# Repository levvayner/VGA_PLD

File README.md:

# VGA Video Card
This project uses TTL components and 2 GALs to create a video card.
There are several parts to the entire development system to aid in development and troubleshooting. Another repository for code that is used on the Arduino Due can be found at https://github.com/levvayner/SRAM-Console

## Parts
 - Hardware Design files in KiCad
 - 2 projects for progamming GAL22V10C PLDs
 - Application used to refine and upload images to the Arduino Due
 - Timing and other documentation
 - Firmware for the Arduino Due to host the video card (https://github.com/levvayner/SRAM-Console)

 ## Getting Started

 ### Prerequisites
 #### Schematics
KiCad software - available for free @ https://www.kicad.org/
 #### Programmable Logic Devices
This can be done with the official Atmel software (https://www.microchip.com/en-us/products/fpgas-and-plds/spld-cplds/pld-design-resources) on windows and using their programmer. 
An alternative approach is to use a cheap progammer like the **TL866+** and using Microsoft Code with the **VS Cupl** extension.
 -http://www.xgecu.com/en/TL866_main.html
-https://marketplace.visualstudio.com/items?itemName=VaynerSystems.VS-Cupl

If choosing the former, follow Atmel's instructions using the included .pld files. If chosing the latter, you can open the workspace and you will see both projects. You can build and deploy the projects right from Code!

You will need to download the Atmel Wincupl progam either way. If you chose to use VS code, you will also need to download and install minipro. More instructions about requirements can be found in the VS Cupl repo https://github.com/levvayner/ATF15xx-cupl

#### Microcontroller
The project uses an Arduino Due uC. The device is low cost, offers a great deal of pins, and has a low price point.

Another device like the Arduino MEGA may suffice. 
Install Microsoft's Code and install the Platform IO extension.
The project can be found here: https://github.com/levvayner/SRAM-Console

## Building the hardware

You can use a breadboard and follow the schematic to build the circuit. First the clock and counters are wired. Then the PLDs are wired to execute combinatory logic to determine timing signals like V-SYNC, H-SYNC, and others like when the screen is not displaying, marking it safe to write to RAM.

The components used in the schematic are available in the KiCad project's output folder.
Currently they are

| Component                 | Source                                                                                 |
| ------------------------- | -------------------------------------------------------------------------------------- |
| Arduino Due               | https://docs.arduino.cc/hardware/due                                                   |
| Capactitor (0805) 560 pf  | ebay, mouser, digikey                                                                  |
| Capacitor Tantalum        | ebay, mouser, digikey                                                                  |
| 2.54mm pins               | ebay, mouser, digikey                                                                  |
| DSUB 15 pin VGA connector | ebay, mouser, digikey                                                                  |
| USB type A connector      | ebay, mouser, digikey                                                                  |
| Resistors (0805)          | ebay, mouser, digikey                                                                  |
| K6X8008T2B-TF55           | https://www.alldatasheet.com/datasheet-pdf/download/85484/SAMSUNG/K6X8008C2B-TF55.html |
| 74HC245D                  | ebay, mouser, digikey                                                                  |
| 74HC161D                  | ebay, mouser, digikey                                                                  |
| 74HC32D                   | ebay, mouser, digikey                                                                  |
| 74HC08D                   | ebay, mouser, digikey                                                                  |
| 74HC00D                   | ebay, mouser, digikey                                                                  |
| 74HC14D                   | ebay, mouser, digikey                                                                  |
| GAL22V10                  | ebay, mouser, digikey                                                                  |
| 16MHz Full can oscillator | ebay, mouser, digikey                                                                  |

### GALs
The programmable logic devices are not absolutely required. They can be replaced by inverters and a few logic gates to determine when a counter should trigger a signal (e.g. h-sync at count 603) and use the counter inputs to determine if that number is reached. Several flip flops can be used for storing the state e.g. store v-sync bit at frame 610, clear at 620.
However you may want to change timings or the clock speed to accomplish a different resolution or pixel density. It is much easier to reprogram the GALS to change timing than to re-wire these logic gates. If you have finalized your design, chaning to logic gates and flip flops is recommended. Even better you can use a magnitude comperator instead of a collection of logic gates.

>To progam the gals, you may need to erase the chip. Some chips come locked, and the programmer software from XGECU has an option to clear it. If your changes don't seem to take affect after programming, use their software to make sure the chip is not locked.

There are two projects included. One is used for the horizontal timing, the other for vertical.

>*There is **VGA_SINGLE_PLD** project that can use an **ATF1504AS** instead of these two, but it has not been verified.*

### Arduino 
The project [VGA Controller](https://github.com/levvayner/SRAM-Console) can be used to interface with and develop the video card further. It has functionality to connect to the controller from its serial port, or connect a PS/2 keyboard (experimental) 

## Roadmap
- Add PS/2 mouse support
- Add second SRAM chip to expand data bus to 16 bit
- Add second SRAM chip to round-robin 2 chips between controller and video output, allowing for controller to read/write to SRAM without interfering with the VGA rendering process.

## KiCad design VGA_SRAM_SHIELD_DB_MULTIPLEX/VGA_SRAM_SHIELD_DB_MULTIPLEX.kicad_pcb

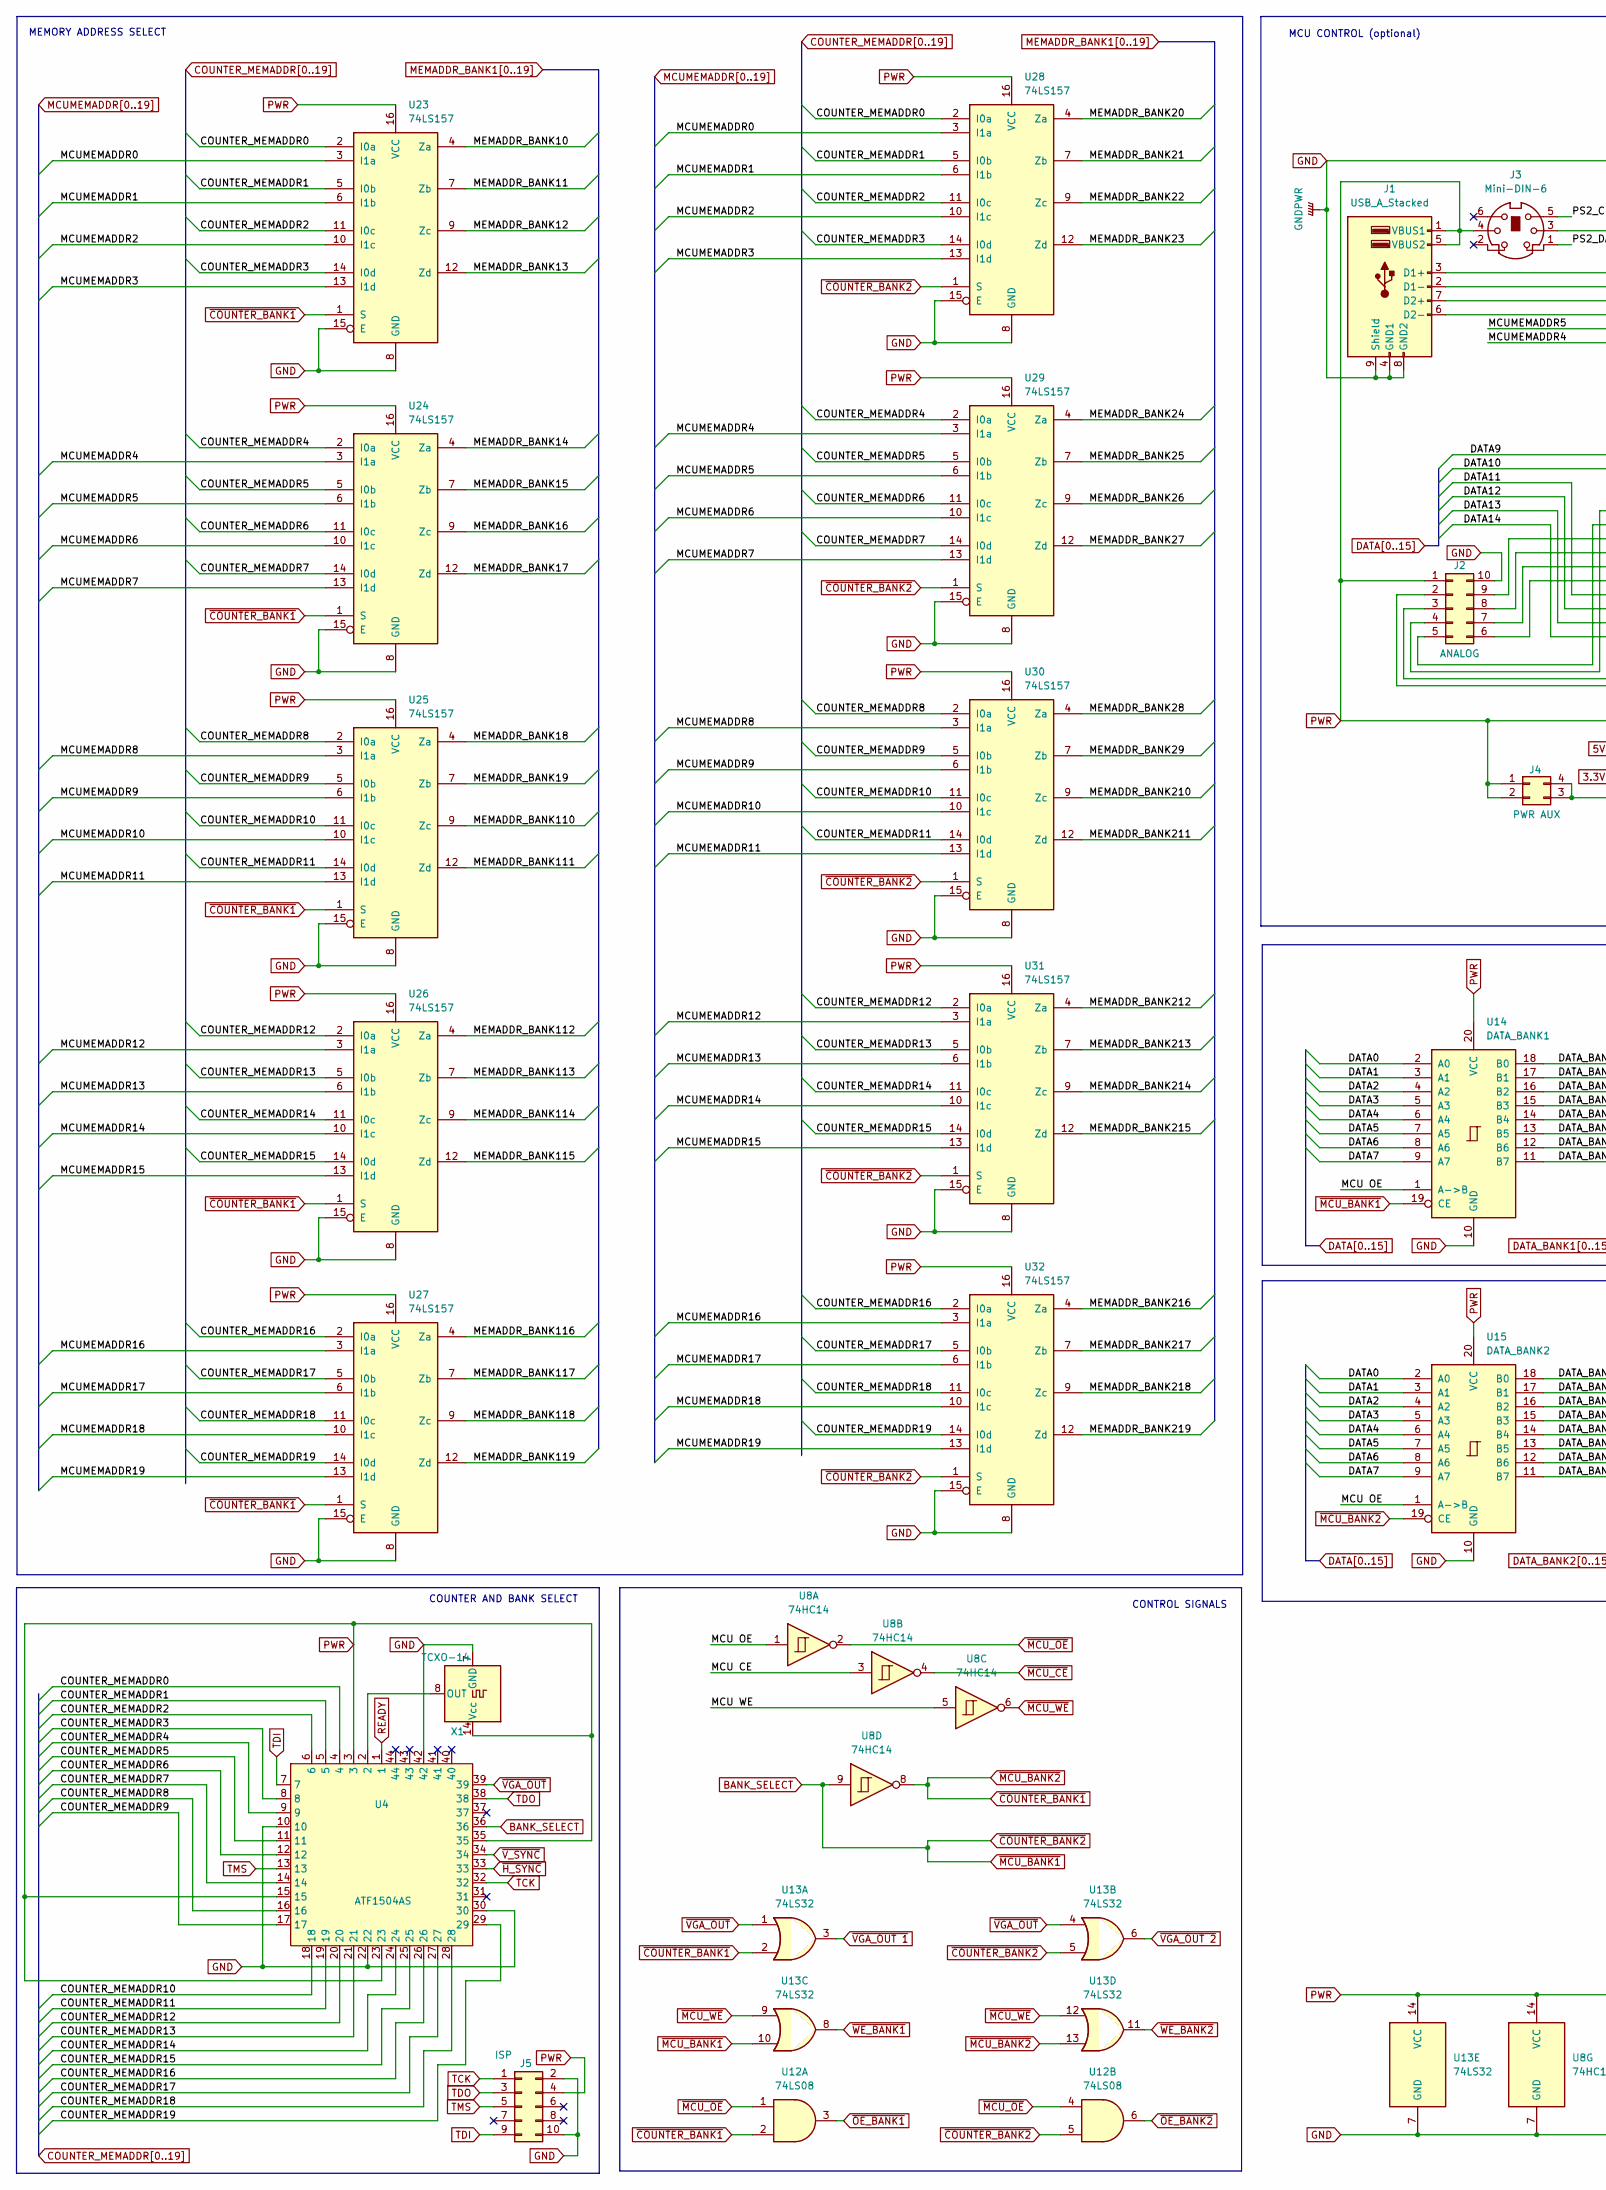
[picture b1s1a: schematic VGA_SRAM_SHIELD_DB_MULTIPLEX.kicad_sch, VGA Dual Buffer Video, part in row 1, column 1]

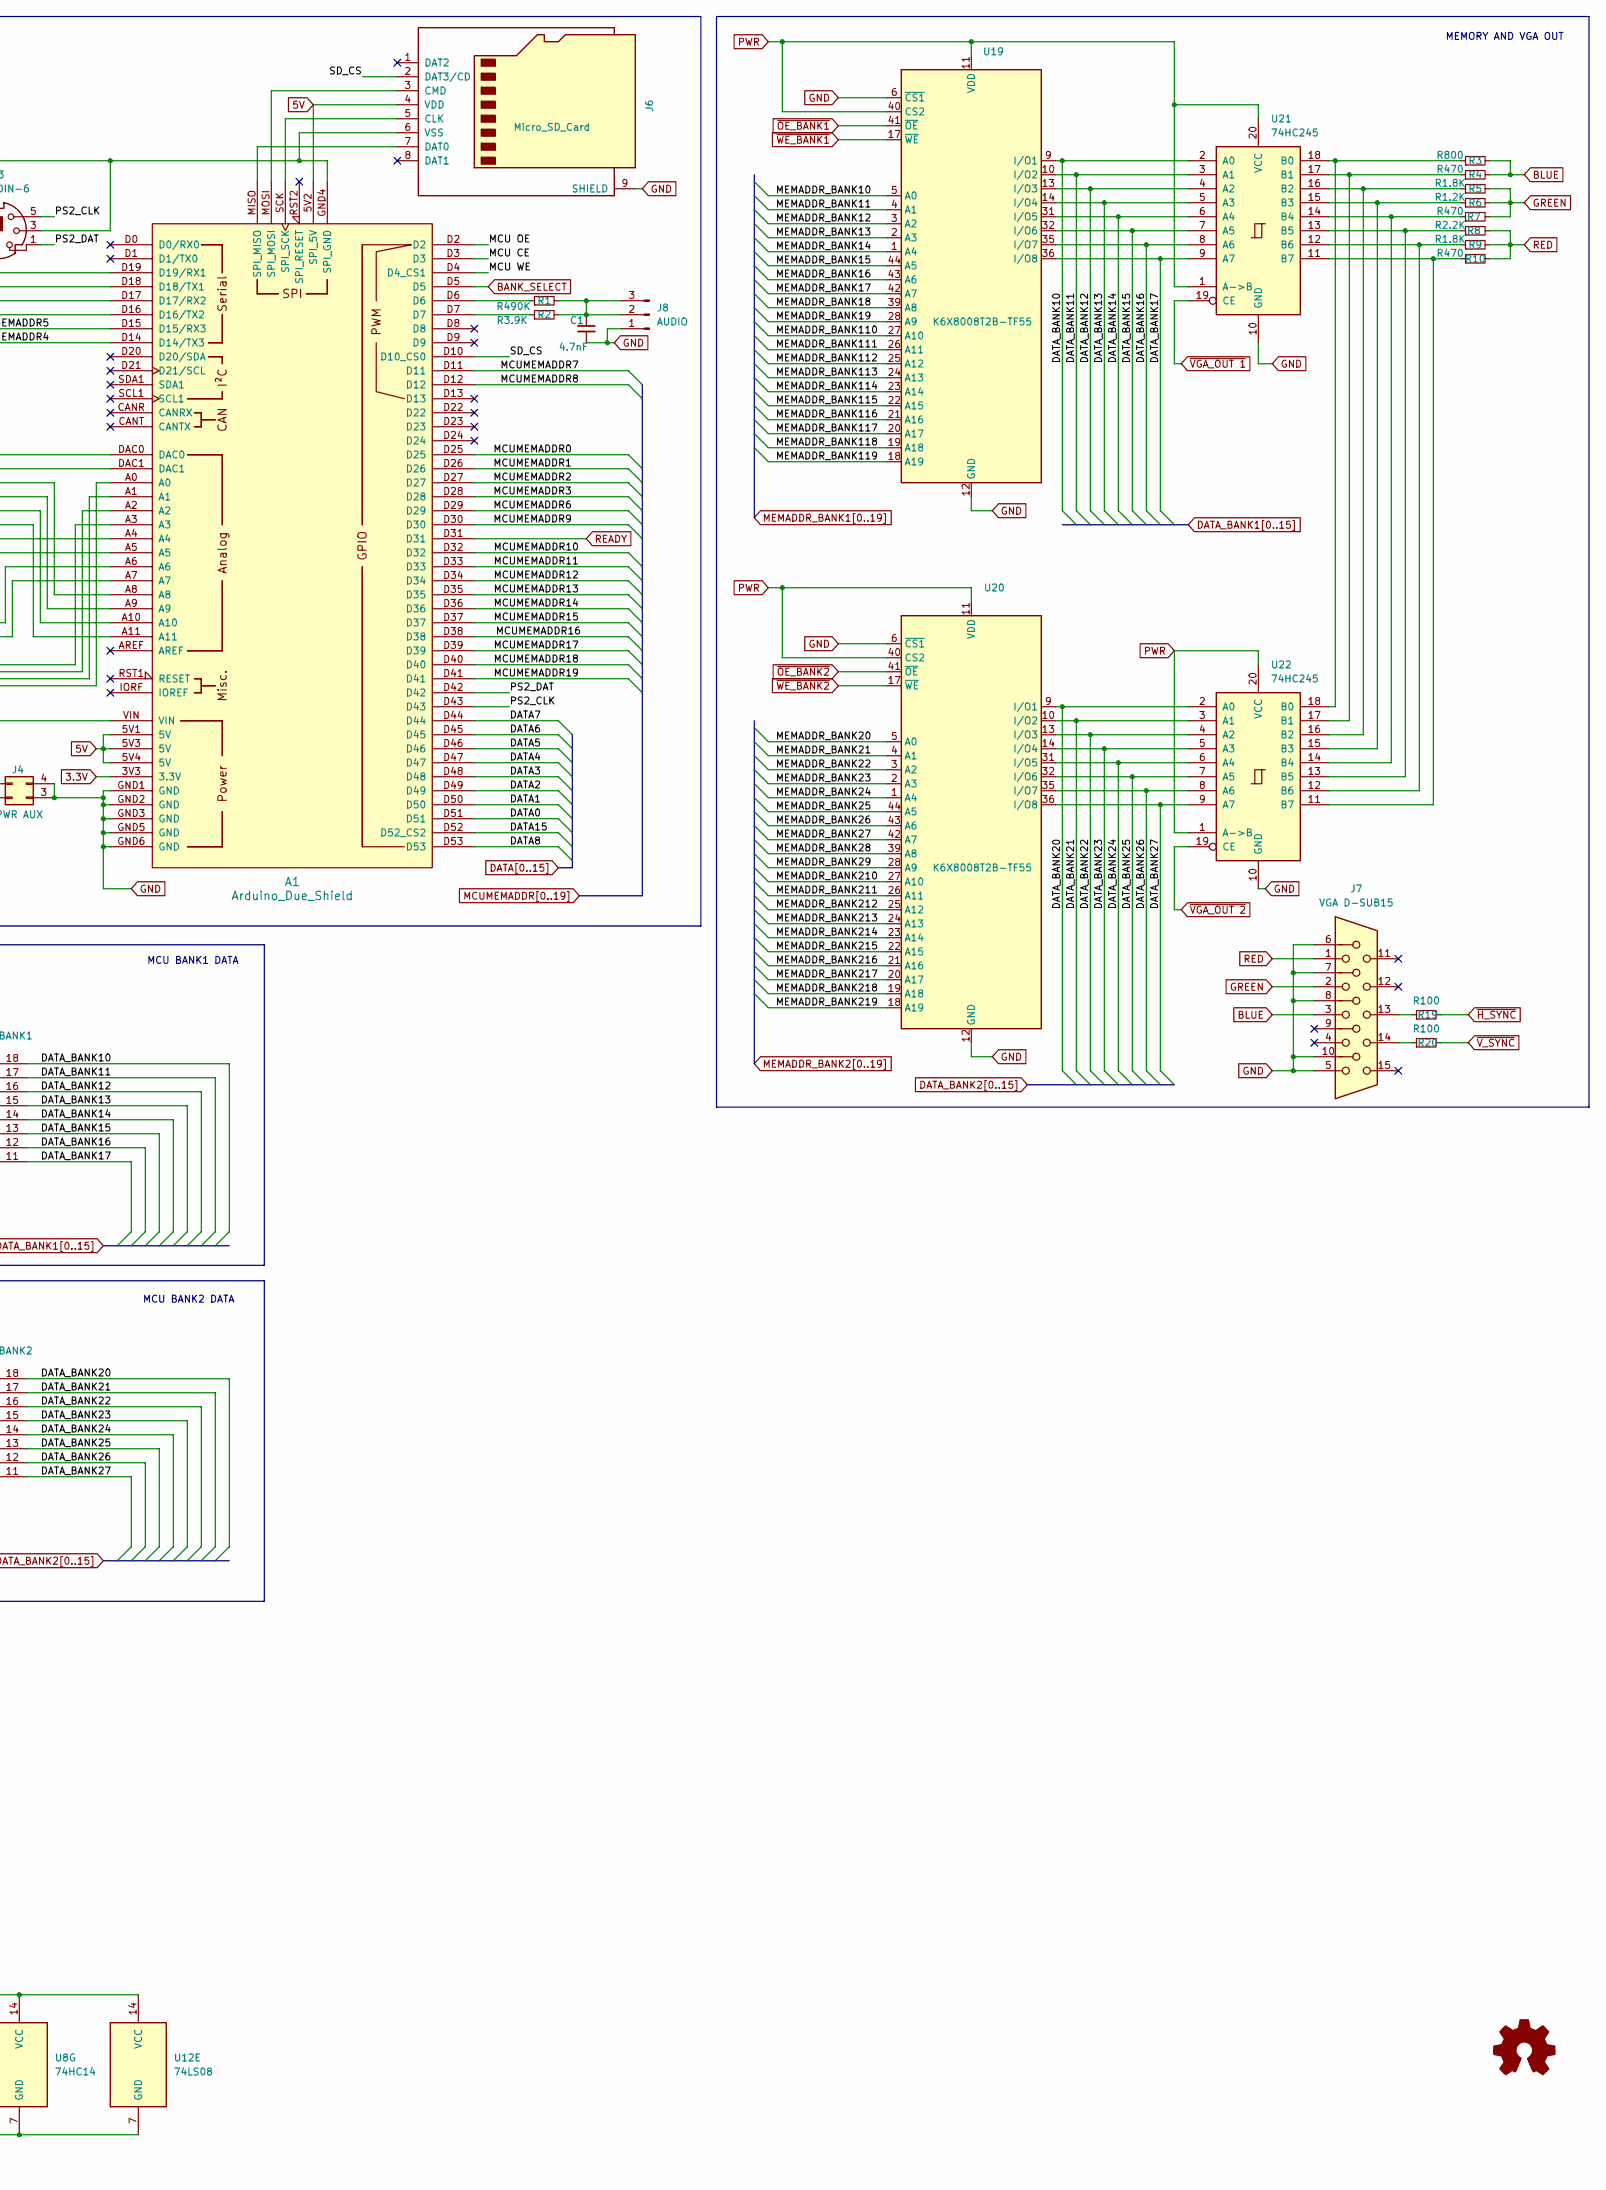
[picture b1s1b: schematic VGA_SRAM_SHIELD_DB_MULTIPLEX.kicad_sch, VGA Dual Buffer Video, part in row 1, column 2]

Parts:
A1: Arduino_Due_Shield
C1: 4.7nF; C_0805_2012Metric
J1: USB_A_Stacked; USB_A_CUI_UJ2-ADH-TH_Horizontal_Stacked
J2: ANALOG; PinSocket_2x05_P2.54mm_Vertical
J3: Mini-DIN-6; mini-DIN 6
J4: PWR AUX; PinSocket_2x02_P2.54mm_Vertical
J5: ISP; PinSocket_2x05_P2.54mm_Vertical
J6: Micro_SD_Card; J_SD_Card-micro_socket_A
J7: VGA D-SUB15; DSUB-15-HD_Female_Horizontal_P2.29x1.98mm_EdgePinOffset8.35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
J8: AUDIO; PinSocket_1x03_P2.54mm_Vertical
R1: R490K; R_0805_2012Metric
R2: R3.9K; R_0805_2012Metric
R3: R800; R_0805_2012Metric
R4, R7, R10: R470; R_0805_2012Metric
R5, R9: R1.8K; R_0805_2012Metric
R6: R1.2K; R_0805_2012Metric
R8: R2.2K; R_0805_2012Metric
R19, R20: R100; R_0805_2012Metric
U4: ATF1504AS; PLCC-44_THT-Socket
U8: 74HC14; SO-14_3.9x8.65mm_P1.27mm
U12: 74LS08; SO-14_3.9x8.65mm_P1.27mm
U13: 74LS32; SO-14_3.9x8.65mm_P1.27mm
U14: DATA_BANK1; SOP-20_7.5x12.8mm_P1.27mm
U15: DATA_BANK2; SOP-20_7.5x12.8mm_P1.27mm
U19, U20: K6X8008T2B-TF55; TSOP-II-44_10.16x18.41mm_P0.8mm
U21, U22: 74HC245; SOP-20_7.5x12.8mm_P1.27mm
U23, U24, U25, U26, U27, U28, U29, U30, U31, U32: 74LS157; SOP-16_3.9x9.9mm_P1.27mm
X1: TCXO-14; Oscillator_DIP-14

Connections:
3.3V: A1.3V3 (3.3V)
5V: A1.5V1 (5V), A1.5V2 (SPI_5V), A1.5V3 (5V), A1.5V4 (5V), J6.4 (VDD)
/MCU CE: A1.D3, U8.3
/MCU OE: A1.D2, U8.1, U14.1 (A->B), U15.1 (A->B)
/MCU WE: A1.D4 (D4_CS1), U8.5
/PS2_CLK: A1.D43, J3.5
/PS2_DAT: A1.D42, J3.1
/SD_CS: A1.D10 (D10_CS0), J6.2 (DAT3/CD)
BANK_SELECT: A1.D5, U4.36, U8.9, U12.5, U13.5, U13.10, U14.19 (CE), U28.1 (S), U29.1 (S), U30.1 (S), U31.1 (S), U32.1 (S)
BLUE: J7.3, R3.2, R4.2
COUNTER_MEMADDR0: U4.4, U23.2 (I0a), U28.2 (I0a)
COUNTER_MEMADDR1: U4.5, U23.5 (I0b), U28.5 (I0b)
COUNTER_MEMADDR2: U4.6, U23.11 (I0c), U28.11 (I0c)
COUNTER_MEMADDR3: U4.8, U23.14 (I0d), U28.14 (I0d)
COUNTER_MEMADDR4: U4.9, U24.2 (I0a), U29.2 (I0a)
COUNTER_MEMADDR5: U4.11, U24.5 (I0b), U29.5 (I0b)
COUNTER_MEMADDR6: U4.12, U24.11 (I0c), U29.11 (I0c)
COUNTER_MEMADDR7: U4.14, U24.14 (I0d), U29.14 (I0d)
COUNTER_MEMADDR8: U4.16, U25.2 (I0a), U30.2 (I0a)
COUNTER_MEMADDR9: U4.17, U25.5 (I0b), U30.5 (I0b)
COUNTER_MEMADDR10: U4.18, U25.11 (I0c), U30.11 (I0c)
COUNTER_MEMADDR11: U4.19, U25.14 (I0d), U30.14 (I0d)
COUNTER_MEMADDR12: U4.20, U26.2 (I0a), U31.2 (I0a)
COUNTER_MEMADDR13: U4.21, U26.5 (I0b), U31.5 (I0b)
COUNTER_MEMADDR14: U4.24, U26.11 (I0c), U31.11 (I0c)
COUNTER_MEMADDR15: U4.25, U26.14 (I0d), U31.14 (I0d)
COUNTER_MEMADDR16: U4.26, U27.2 (I0a), U32.2 (I0a)
COUNTER_MEMADDR17: U4.27, U27.5 (I0b), U32.5 (I0b)
COUNTER_MEMADDR18: U4.28, U27.11 (I0c), U32.11 (I0c)
COUNTER_MEMADDR19: U4.29, U27.14 (I0d), U32.14 (I0d)
DATA0: A1.D51, U14.2 (A0), U15.2 (A0)
DATA1: A1.D50, U14.3 (A1), U15.3 (A1)
DATA2: A1.D49, U14.4 (A2), U15.4 (A2)
DATA3: A1.D48, U14.5 (A3), U15.5 (A3)
DATA4: A1.D47, U14.6 (A4), U15.6 (A4)
DATA5: A1.D46, U14.7 (A5), U15.7 (A5)
DATA6: A1.D45, U14.8 (A6), U15.8 (A6)
DATA7: A1.D44, U14.9 (A7), U15.9 (A7)
DATA8: A1.D53
DATA9: A1.DAC0
DATA10: A1.DAC1
DATA11: A1.A8
DATA12: A1.A9
DATA13: A1.A10
DATA14: A1.A11
DATA15: A1.D52 (D52_CS2)
DATA_BANK10: U14.18 (B0), U19.9 (I/O1), U21.2 (A0)
DATA_BANK11: U14.17 (B1), U19.10 (I/O2), U21.3 (A1)
DATA_BANK12: U14.16 (B2), U19.13 (I/O3), U21.4 (A2)
DATA_BANK13: U14.15 (B3), U19.14 (I/O4), U21.5 (A3)
DATA_BANK14: U14.14 (B4), U19.31 (I/O5), U21.6 (A4)
DATA_BANK15: U14.13 (B5), U19.32 (I/O6), U21.7 (A5)
DATA_BANK16: U14.12 (B6), U19.35 (I/O7), U21.8 (A6)
DATA_BANK17: U14.11 (B7), U19.36 (I/O8), U21.9 (A7)
DATA_BANK20: U15.18 (B0), U20.9 (I/O1), U22.2 (A0)
DATA_BANK21: U15.17 (B1), U20.10 (I/O2), U22.3 (A1)
DATA_BANK22: U15.16 (B2), U20.13 (I/O3), U22.4 (A2)
DATA_BANK23: U15.15 (B3), U20.14 (I/O4), U22.5 (A3)
DATA_BANK24: U15.14 (B4), U20.31 (I/O5), U22.6 (A4)
DATA_BANK25: U15.13 (B5), U20.32 (I/O6), U22.7 (A5)
DATA_BANK26: U15.12 (B6), U20.35 (I/O7), U22.8 (A6)
DATA_BANK27: U15.11 (B7), U20.36 (I/O8), U22.9 (A7)
GND: A1.GND1 (GND), A1.GND2 (GND), A1.GND3 (GND), A1.GND4 (SPI_GND), A1.GND5 (GND), A1.GND6 (GND), C1.2, J1.4 (GND1), J1.8 (GND2), J1.9 (Shield), J2.10, J3.3, J4.3, J4.4, J5.2, J5.10, J6.6 (VSS), J6.9 (SHIELD), J7.5, J7.6, J7.7, J7.8, J7.10, J8.1, U4.10, U4.22, U4.30, U4.42, U8.7 (GND), U12.7 (GND), U13.7 (GND), U14.10 (GND), U15.10 (GND), U19.6 (~CS1), U19.12 (GND), U19.34 (GND), U20.6 (~CS1), U20.12 (GND), U20.34 (GND), U21.10 (GND), U22.10 (GND), U23.8 (GND), U23.15 (E), U24.8 (GND), U24.15 (E), U25.8 (GND), U25.15 (E), U26.8 (GND), U26.15 (E), U27.8 (GND), U27.15 (E), U28.8 (GND), U28.15 (E), U29.8 (GND), U29.15 (E), U30.8 (GND), U30.15 (E), U31.8 (GND), U31.15 (E), U32.8 (GND), U32.15 (E), X1.7 (GND)
GREEN: J7.2, R5.2, R6.2, R7.2
MCUMEMADDR0: A1.D25, U23.3 (I1a), U28.3 (I1a)
MCUMEMADDR1: A1.D26, U23.6 (I1b), U28.6 (I1b)
MCUMEMADDR2: A1.D27, U23.10 (I1c), U28.10 (I1c)
MCUMEMADDR3: A1.D28, U23.13 (I1d), U28.13 (I1d)
MCUMEMADDR4: A1.D14 (D14/TX3), U24.3 (I1a), U29.3 (I1a)
MCUMEMADDR5: A1.D15 (D15/RX3), U24.6 (I1b), U29.6 (I1b)
MCUMEMADDR6: A1.D29, U24.10 (I1c), U29.10 (I1c)
MCUMEMADDR7: A1.D11, U24.13 (I1d), U29.13 (I1d)
MCUMEMADDR8: A1.D12, U25.3 (I1a), U30.3 (I1a)
MCUMEMADDR9: A1.D30, U25.6 (I1b), U30.6 (I1b)
MCUMEMADDR10: A1.D32, U25.10 (I1c), U30.10 (I1c)
MCUMEMADDR11: A1.D33, U25.13 (I1d), U30.13 (I1d)
MCUMEMADDR12: A1.D34, U26.3 (I1a), U31.3 (I1a)
MCUMEMADDR13: A1.D35, U26.6 (I1b), U31.6 (I1b)
MCUMEMADDR14: A1.D36, U26.10 (I1c), U31.10 (I1c)
MCUMEMADDR15: A1.D37, U26.13 (I1d), U31.13 (I1d)
MCUMEMADDR16: A1.D38, U27.3 (I1a), U32.3 (I1a)
MCUMEMADDR17: A1.D39, U27.6 (I1b), U32.6 (I1b)
MCUMEMADDR18: A1.D40, U27.10 (I1c), U32.10 (I1c)
MCUMEMADDR19: A1.D41, U27.13 (I1d), U32.13 (I1d)
MEMADDR_BANK10: U19.5 (A0), U23.4 (Za)
MEMADDR_BANK11: U19.4 (A1), U23.7 (Zb)
MEMADDR_BANK12: U19.3 (A2), U23.9 (Zc)
MEMADDR_BANK13: U19.2 (A3), U23.12 (Zd)
MEMADDR_BANK14: U19.1 (A4), U24.4 (Za)
MEMADDR_BANK15: U19.44 (A5), U24.7 (Zb)
MEMADDR_BANK16: U19.43 (A6), U24.9 (Zc)
MEMADDR_BANK17: U19.42 (A7), U24.12 (Zd)
MEMADDR_BANK18: U19.39 (A8), U25.4 (Za)
MEMADDR_BANK19: U19.28 (A9), U25.7 (Zb)
MEMADDR_BANK20: U20.5 (A0), U28.4 (Za)
MEMADDR_BANK21: U20.4 (A1), U28.7 (Zb)
MEMADDR_BANK22: U20.3 (A2), U28.9 (Zc)
MEMADDR_BANK23: U20.2 (A3), U28.12 (Zd)
MEMADDR_BANK24: U20.1 (A4), U29.4 (Za)
MEMADDR_BANK25: U20.44 (A5), U29.7 (Zb)
MEMADDR_BANK26: U20.43 (A6), U29.9 (Zc)
MEMADDR_BANK27: U20.42 (A7), U29.12 (Zd)
MEMADDR_BANK28: U20.39 (A8), U30.4 (Za)
MEMADDR_BANK29: U20.28 (A9), U30.7 (Zb)
MEMADDR_BANK110: U19.27 (A10), U25.9 (Zc)
MEMADDR_BANK111: U19.26 (A11), U25.12 (Zd)
MEMADDR_BANK112: U19.25 (A12), U26.4 (Za)
MEMADDR_BANK113: U19.24 (A13), U26.7 (Zb)
MEMADDR_BANK114: U19.23 (A14), U26.9 (Zc)
MEMADDR_BANK115: U19.22 (A15), U26.12 (Zd)
MEMADDR_BANK116: U19.21 (A16), U27.4 (Za)
MEMADDR_BANK117: U19.20 (A17), U27.7 (Zb)
MEMADDR_BANK118: U19.19 (A18), U27.9 (Zc)
MEMADDR_BANK119: U19.18 (A19), U27.12 (Zd)
MEMADDR_BANK210: U20.27 (A10), U30.9 (Zc)
MEMADDR_BANK211: U20.26 (A11), U30.12 (Zd)
MEMADDR_BANK212: U20.25 (A12), U31.4 (Za)
MEMADDR_BANK213: U20.24 (A13), U31.7 (Zb)
MEMADDR_BANK214: U20.23 (A14), U31.9 (Zc)
MEMADDR_BANK215: U20.22 (A15), U31.12 (Zd)
MEMADDR_BANK216: U20.21 (A16), U32.4 (Za)
MEMADDR_BANK217: U20.20 (A17), U32.7 (Zb)
MEMADDR_BANK218: U20.19 (A18), U32.9 (Zc)
MEMADDR_BANK219: U20.18 (A19), U32.12 (Zd)
unnamed: A1.D16 (D16/TX2), J1.6 (D2-)
unnamed: A1.D17 (D17/RX2), J1.7 (D2+)
unnamed: A1.D18 (D18/TX1), J1.2 (D1-)
unnamed: A1.D19 (D19/RX1), J1.3 (D1+)
unnamed: A1.D6, R1.1
unnamed: A1.D7, R2.1
unnamed: A1.MISO (SPI_MISO), J6.7 (DAT0)
unnamed: A1.MOSI (SPI_MOSI), J6.3 (CMD)
unnamed: A1.SCK (SPI_SCK), J6.5 (CLK)
unnamed: A1.A0, J2.2
unnamed: A1.A1, J2.3
unnamed: A1.A2, J2.4
unnamed: A1.A3, J2.5
unnamed: A1.A7, J2.6
unnamed: A1.A6, J2.7
unnamed: A1.A5, J2.8
unnamed: A1.A4, J2.9
unnamed: J7.13, R19.1
unnamed: J7.14, R20.1
unnamed: C1.1, J8.2, J8.3, R1.2, R2.2
unnamed: R3.1, U21.18 (B0), U22.18 (B0)
unnamed: R4.1, U21.17 (B1), U22.17 (B1)
unnamed: R5.1, U21.16 (B2), U22.16 (B2)
unnamed: R6.1, U21.15 (B3), U22.15 (B3)
unnamed: R7.1, U21.14 (B4), U22.14 (B4)
unnamed: R8.1, U21.13 (B5), U22.13 (B5)
unnamed: R9.1, U21.12 (B6), U22.12 (B6)
unnamed: R10.1, U21.11 (B7), U22.11 (B7)
unnamed: U4.2, X1.8 (OUT)
PWR: A1.VIN, J1.1 (VBUS1), J1.5 (VBUS2), J2.1, J3.4, J4.1, J4.2, J5.4, U4.3, U4.15, U4.23, U4.35, U8.14 (VCC), U12.14 (VCC), U13.14 (VCC), U14.20 (VCC), U15.20 (VCC), U19.11 (VDD), U19.33 (VDD), U19.40 (CS2), U20.11 (VDD), U20.33 (VDD), U20.40 (CS2), U21.1 (A->B), U21.20 (VCC), U22.1 (A->B), U22.20 (VCC), U23.16 (VCC), U24.16 (VCC), U25.16 (VCC), U26.16 (VCC), U27.16 (VCC), U28.16 (VCC), U29.16 (VCC), U30.16 (VCC), U31.16 (VCC), U32.16 (VCC), X1.14 (Vcc)
READY: A1.D31, U4.1
RED: J7.1, R8.2, R9.2, R10.2
TCK: J5.1, U4.32
TDI: J5.9, U4.7
TDO: J5.3, U4.38
TMS: J5.5, U4.13
~COUNTER_BANK1: U8.8, U12.2, U13.2, U13.13, U15.19 (CE), U23.1 (S), U24.1 (S), U25.1 (S), U26.1 (S), U27.1 (S)
~H_SYNC: R19.2, U4.33
~MCU_CE: U8.4
~MCU_OE: U8.2, U12.1, U12.4
~MCU_WE: U8.6, U13.9, U13.12
~OE_BANK1: U12.3, U19.41 (~OE)
~OE_BANK2: U12.6, U20.41 (~OE)
~VGA_OUT 1: U13.3, U21.19 (CE)
~VGA_OUT 2: U13.6, U22.19 (CE)
~VGA_OUT: U4.39, U13.1, U13.4
~V_SYNC: R20.2, U4.34
~WE_BANK1: U13.8, U19.17 (~WE)
~WE_BANK2: U13.11, U20.17 (~WE)

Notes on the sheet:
MEMORY ADDRESS SELECT
MCU BANK1 DATA
MEMORY AND VGA OUT
MCU BANK2 DATA
MCU CONTROL (optional)
COUNTER AND BANK SELECT
CONTROL SIGNALS

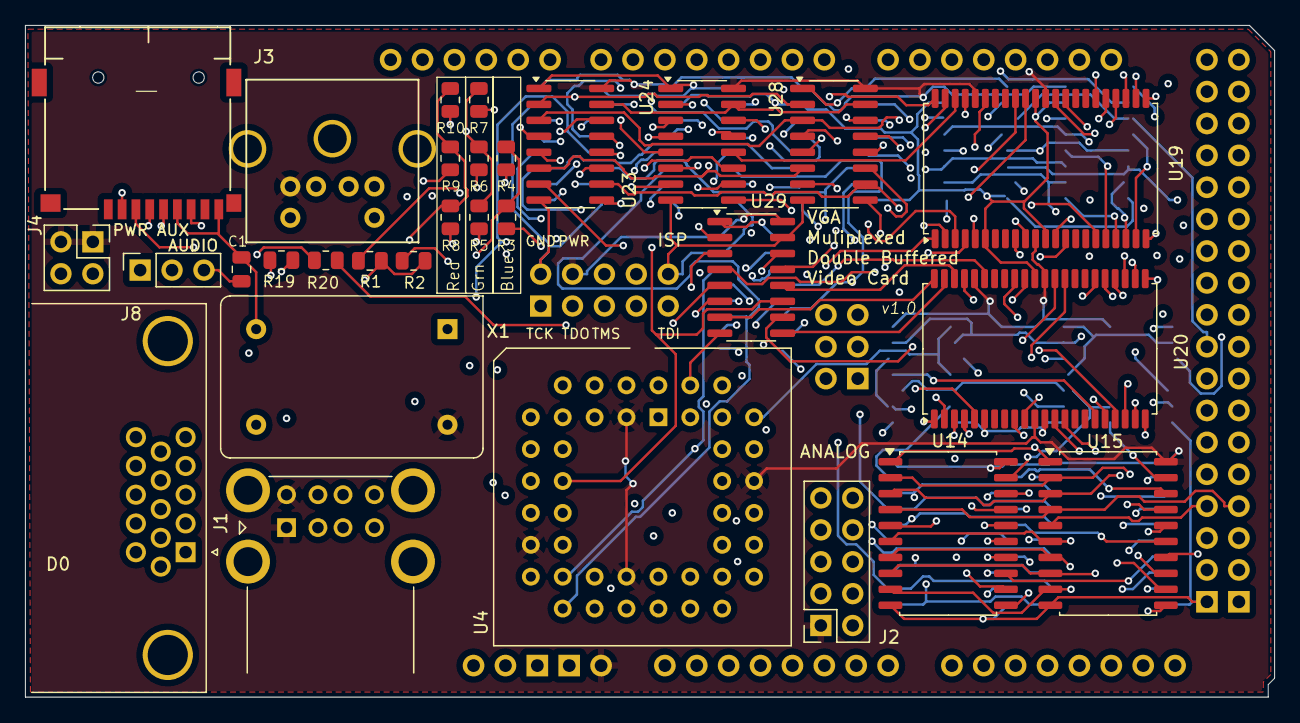
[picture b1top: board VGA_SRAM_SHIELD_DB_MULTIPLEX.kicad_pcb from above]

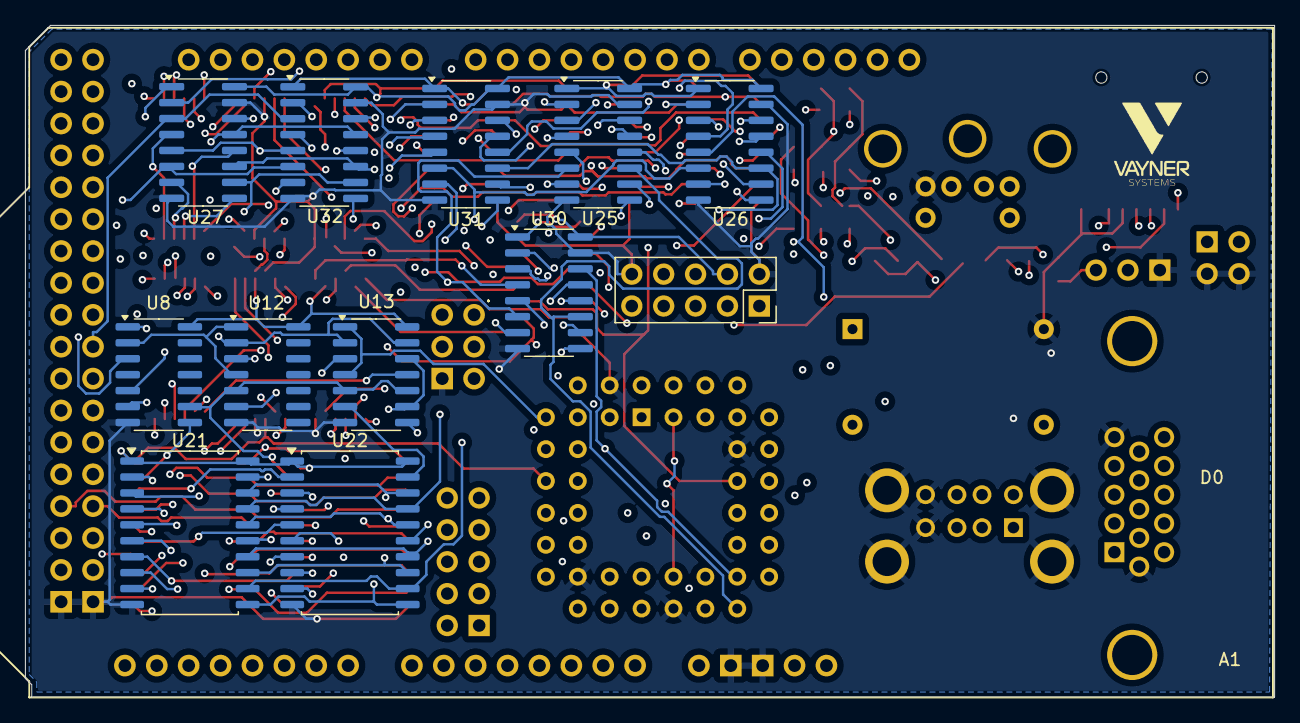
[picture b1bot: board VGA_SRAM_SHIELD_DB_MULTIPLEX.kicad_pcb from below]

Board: 6 copper layers, 99.5 x 53.5 mm, 43 parts (12 on the bottom side), 163 nets.
